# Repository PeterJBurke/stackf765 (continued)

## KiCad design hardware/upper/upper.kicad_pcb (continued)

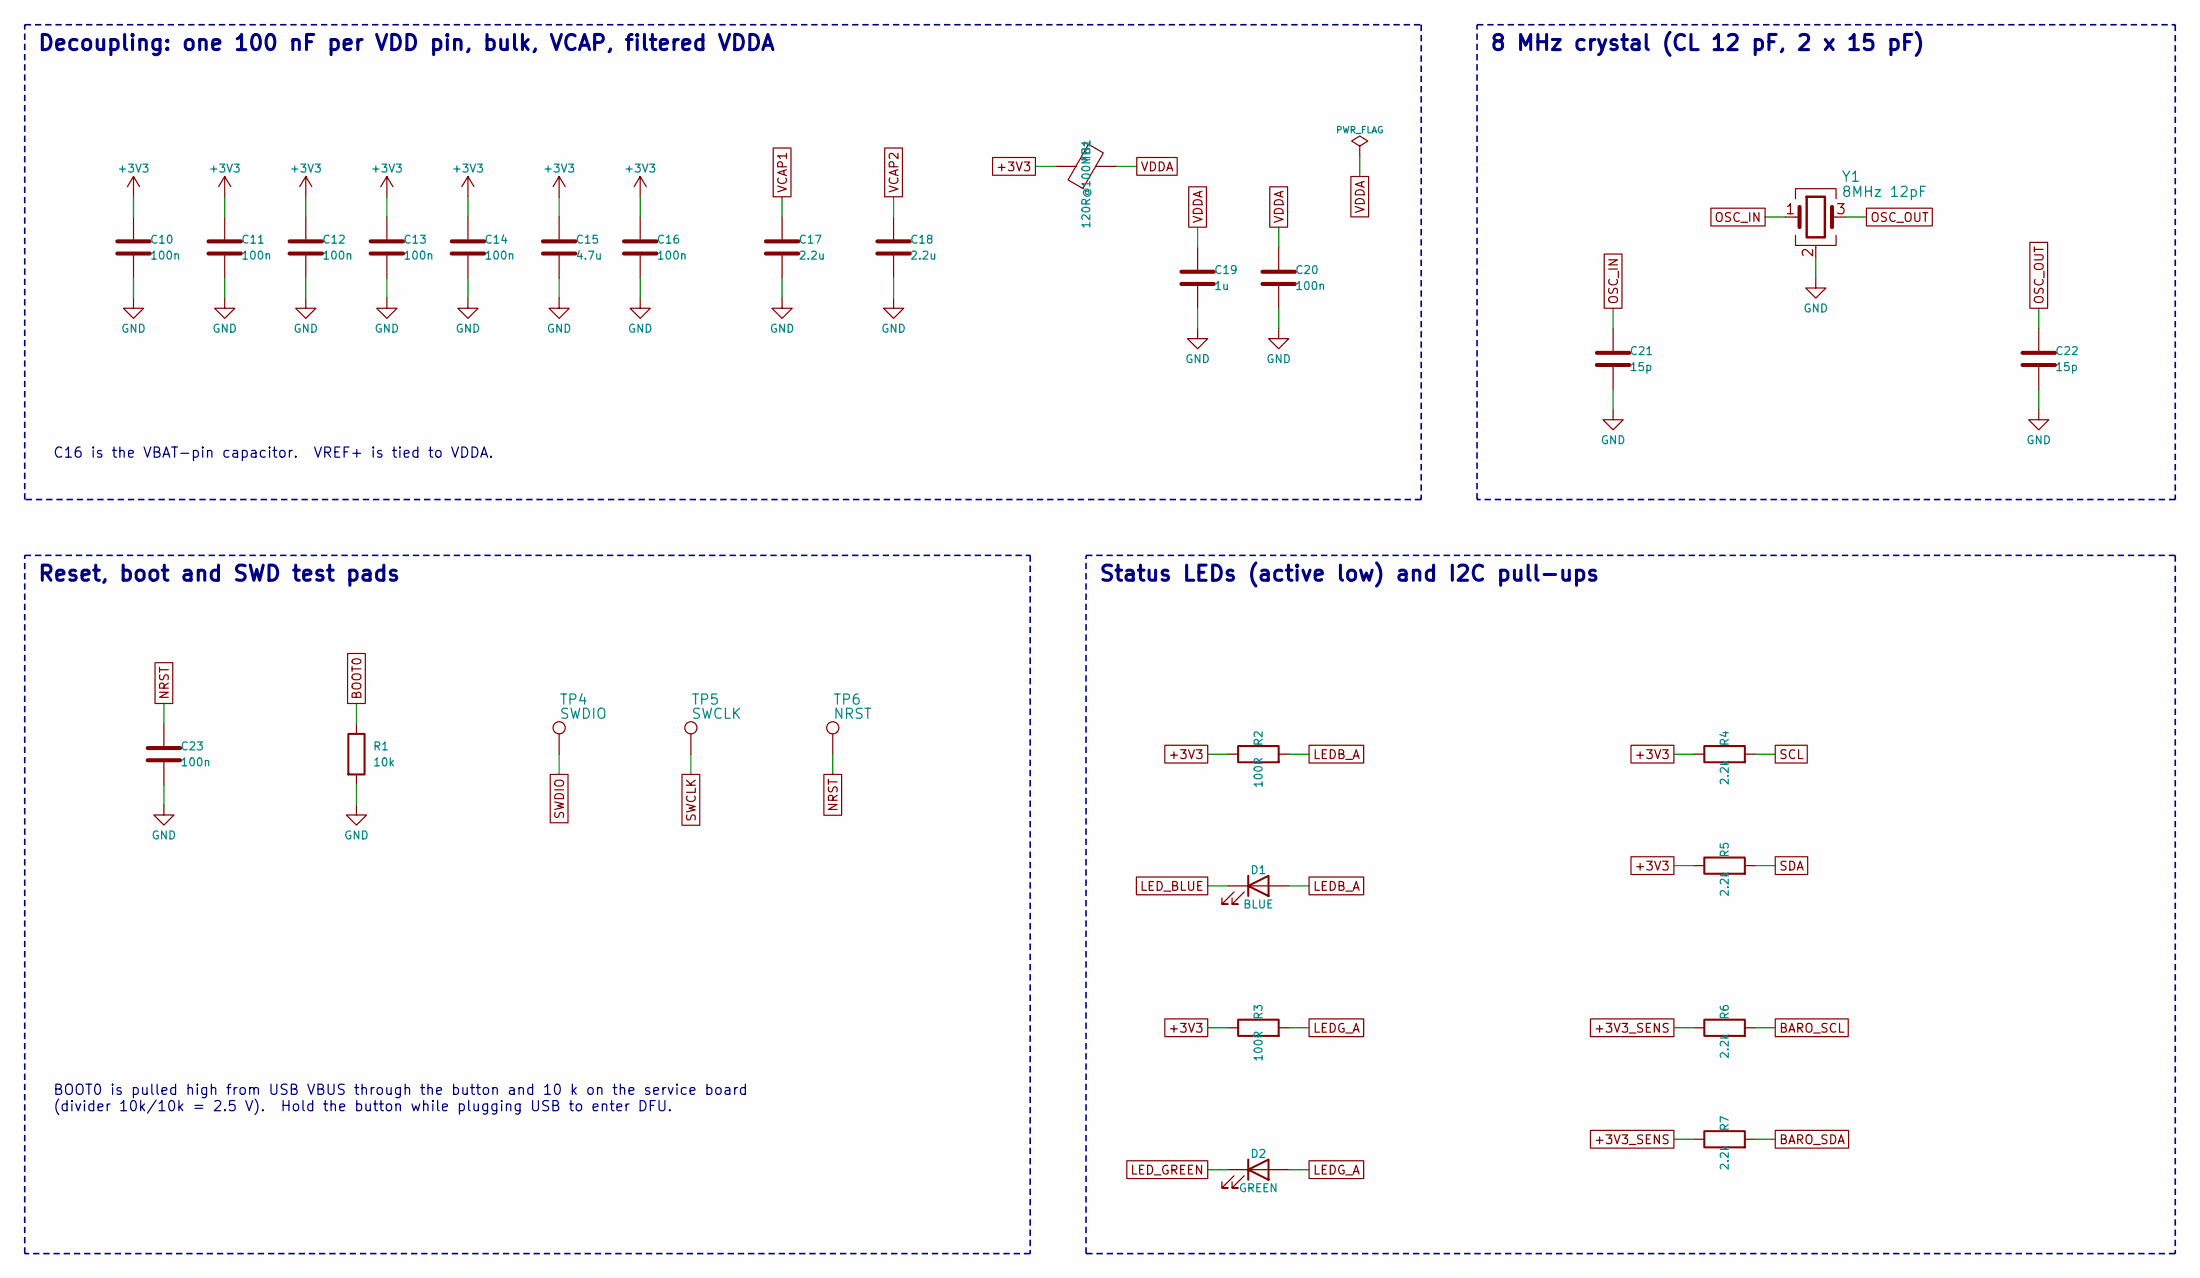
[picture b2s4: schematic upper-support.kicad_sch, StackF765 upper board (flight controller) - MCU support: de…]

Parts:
C10, C11, C12, C13, C14, C16, C20, C23: 100n; C_0402_1005Metric; MPN CL05B104KO5NNNC; LCSC C1525
C15: 4.7u; C_0603_1608Metric; MPN CL10A475KO8NNNC; LCSC C19666
C17, C18: 2.2u; C_0402_1005Metric; MPN CL05A225MQ5NSNC; LCSC C12530
C19: 1u; C_0402_1005Metric; MPN CL05A105KA5NQNC; LCSC C52923
C21, C22: 15p; C_0402_1005Metric; MPN 0402CG150J500NT; LCSC C1548
D1: BLUE; LED_0603_1608Metric; MPN NCD0603B1; LCSC C84266
D2: GREEN; LED_0603_1608Metric; MPN NCD0603G1; LCSC C84267
FB1: 120R@100MHz; L_0603_1608Metric; MPN BLM18PG121SN1D; LCSC C14709
R1: 10k; R_0402_1005Metric; MPN 0402WGF1002TCE; LCSC C25744
R2, R3: 100R; R_0402_1005Metric; MPN 0402WGF1000TCE; LCSC C25076
R4, R5, R6, R7: 2.2k; R_0402_1005Metric; MPN 0402WGF2201TCE; LCSC C25879
TP4: SWDIO; TestPoint_Pad_D1.0mm
TP5: SWCLK; TestPoint_Pad_D1.0mm
TP6: NRST; TestPoint_Pad_D1.0mm
Y1: 8MHz 12pF; Crystal_SMD_3225-4Pin_3.2x2.5mm; MPN XL2EL89COI-111YLC-8M; LCSC C2973805

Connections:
+3V3: C10.1, C11.1, C12.1, C13.1, C14.1, C15.1, C16.1, FB1.1, R2.1, R3.1, R4.1, R5.1; also elsewhere on the board
+3V3_SENS: R6.1, R7.1; also elsewhere on the board
BARO_SCL: R6.2; also elsewhere on the board
BARO_SDA: R7.2; also elsewhere on the board
BOOT0: R1.1; also elsewhere on the board
GND: C10.2, C11.2, C12.2, C13.2, C14.2, C15.2, C16.2, C17.2, C18.2, C19.2, C20.2, C21.2, C22.2, C23.2, R1.2, Y1.2 (G), Y1.4 (G); also elsewhere on the board
LEDB_A: D1.2 (A), R2.2
LEDG_A: D2.2 (A), R3.2
LED_BLUE: D1.1 (K); also elsewhere on the board
LED_GREEN: D2.1 (K); also elsewhere on the board
NRST: C23.1, TP6.1; also elsewhere on the board
OSC_IN: C21.1, Y1.1; also elsewhere on the board
OSC_OUT: C22.1, Y1.3; also elsewhere on the board
SCL: R4.2; also elsewhere on the board
SDA: R5.2; also elsewhere on the board
SWCLK: TP5.1; also elsewhere on the board
SWDIO: TP4.1; also elsewhere on the board
VCAP1: C17.1; also elsewhere on the board
VCAP2: C18.1; also elsewhere on the board
VDDA: C19.1, C20.1, FB1.2; also elsewhere on the board

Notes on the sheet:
Decoupling: one 100 nF per VDD pin, bulk, VCAP, filtered VDDA
C16 is the VBAT-pin capacitor. VREF+ is tied to VDDA.
8 MHz crystal (CL 12 pF, 2 x 15 pF)
Reset, boot and SWD test pads
BOOT0 is pulled high from USB VBUS through the button and 10 k on the service board (divider 10k/10k = 2.5 V). Hold the button while plugging USB to enter DFU.
Status LEDs (active low) and I2C pull-ups

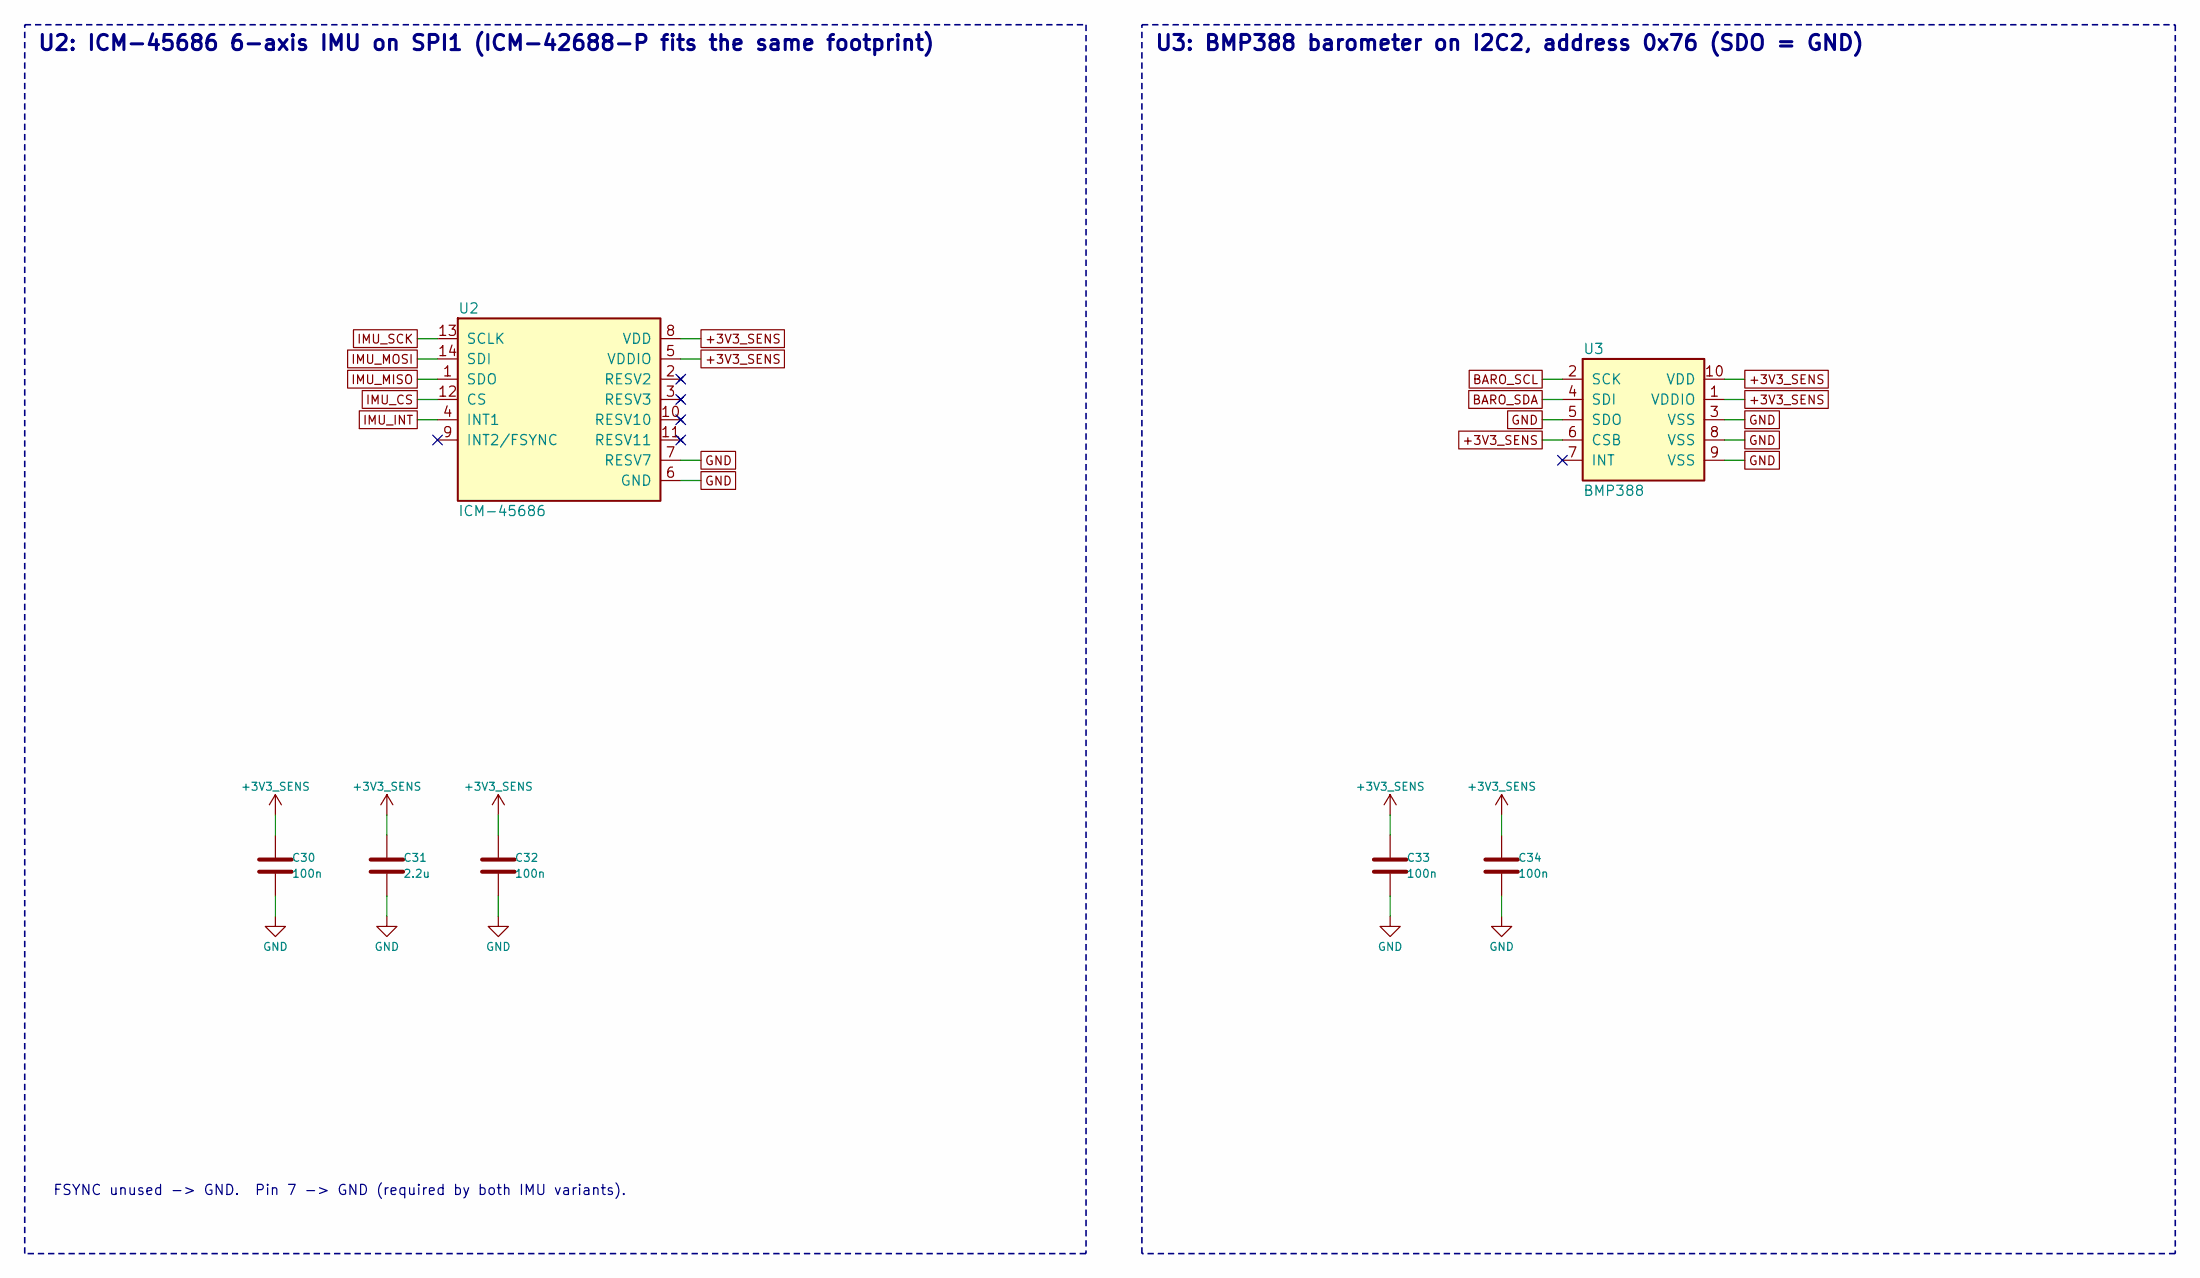
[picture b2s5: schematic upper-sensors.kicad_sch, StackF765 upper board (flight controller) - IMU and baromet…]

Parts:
C30, C32, C33, C34: 100n; C_0402_1005Metric; MPN CL05B104KO5NNNC; LCSC C1525
C31: 2.2u; C_0402_1005Metric; MPN CL05A225MQ5NSNC; LCSC C12530
U2: ICM-45686; LGA-14_3x2.5mm_P0.5mm_LayoutBorder3x4y; MPN ICM-45686; LCSC C22459454
U3: BMP388; Bosch_LGA-10_2x2mm_P0.5mm; MPN BMP388; LCSC C779278

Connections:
+3V3_SENS: C30.1, C31.1, C32.1, C33.1, C34.1, U2.5 (VDDIO), U2.8 (VDD), U3.1 (VDDIO), U3.6 (CSB), U3.10 (VDD); also elsewhere on the board
BARO_SCL: U3.2 (SCK); also elsewhere on the board
BARO_SDA: U3.4 (SDI); also elsewhere on the board
GND: C30.2, C31.2, C32.2, C33.2, C34.2, U2.6 (GND), U2.7 (RESV7), U3.3 (VSS), U3.5 (SDO), U3.8 (VSS), U3.9 (VSS); also elsewhere on the board
IMU_CS: U2.12 (CS); also elsewhere on the board
IMU_INT: U2.4 (INT1); also elsewhere on the board
IMU_MISO: U2.1 (SDO); also elsewhere on the board
IMU_MOSI: U2.14 (SDI); also elsewhere on the board
IMU_SCK: U2.13 (SCLK); also elsewhere on the board

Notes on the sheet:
U2: ICM-45686 6-axis IMU on SPI1 (ICM-42688-P fits the same footprint)
FSYNC unused -> GND. Pin 7 -> GND (required by both IMU variants).
U3: BMP388 barometer on I2C2, address 0x76 (SDO = GND)

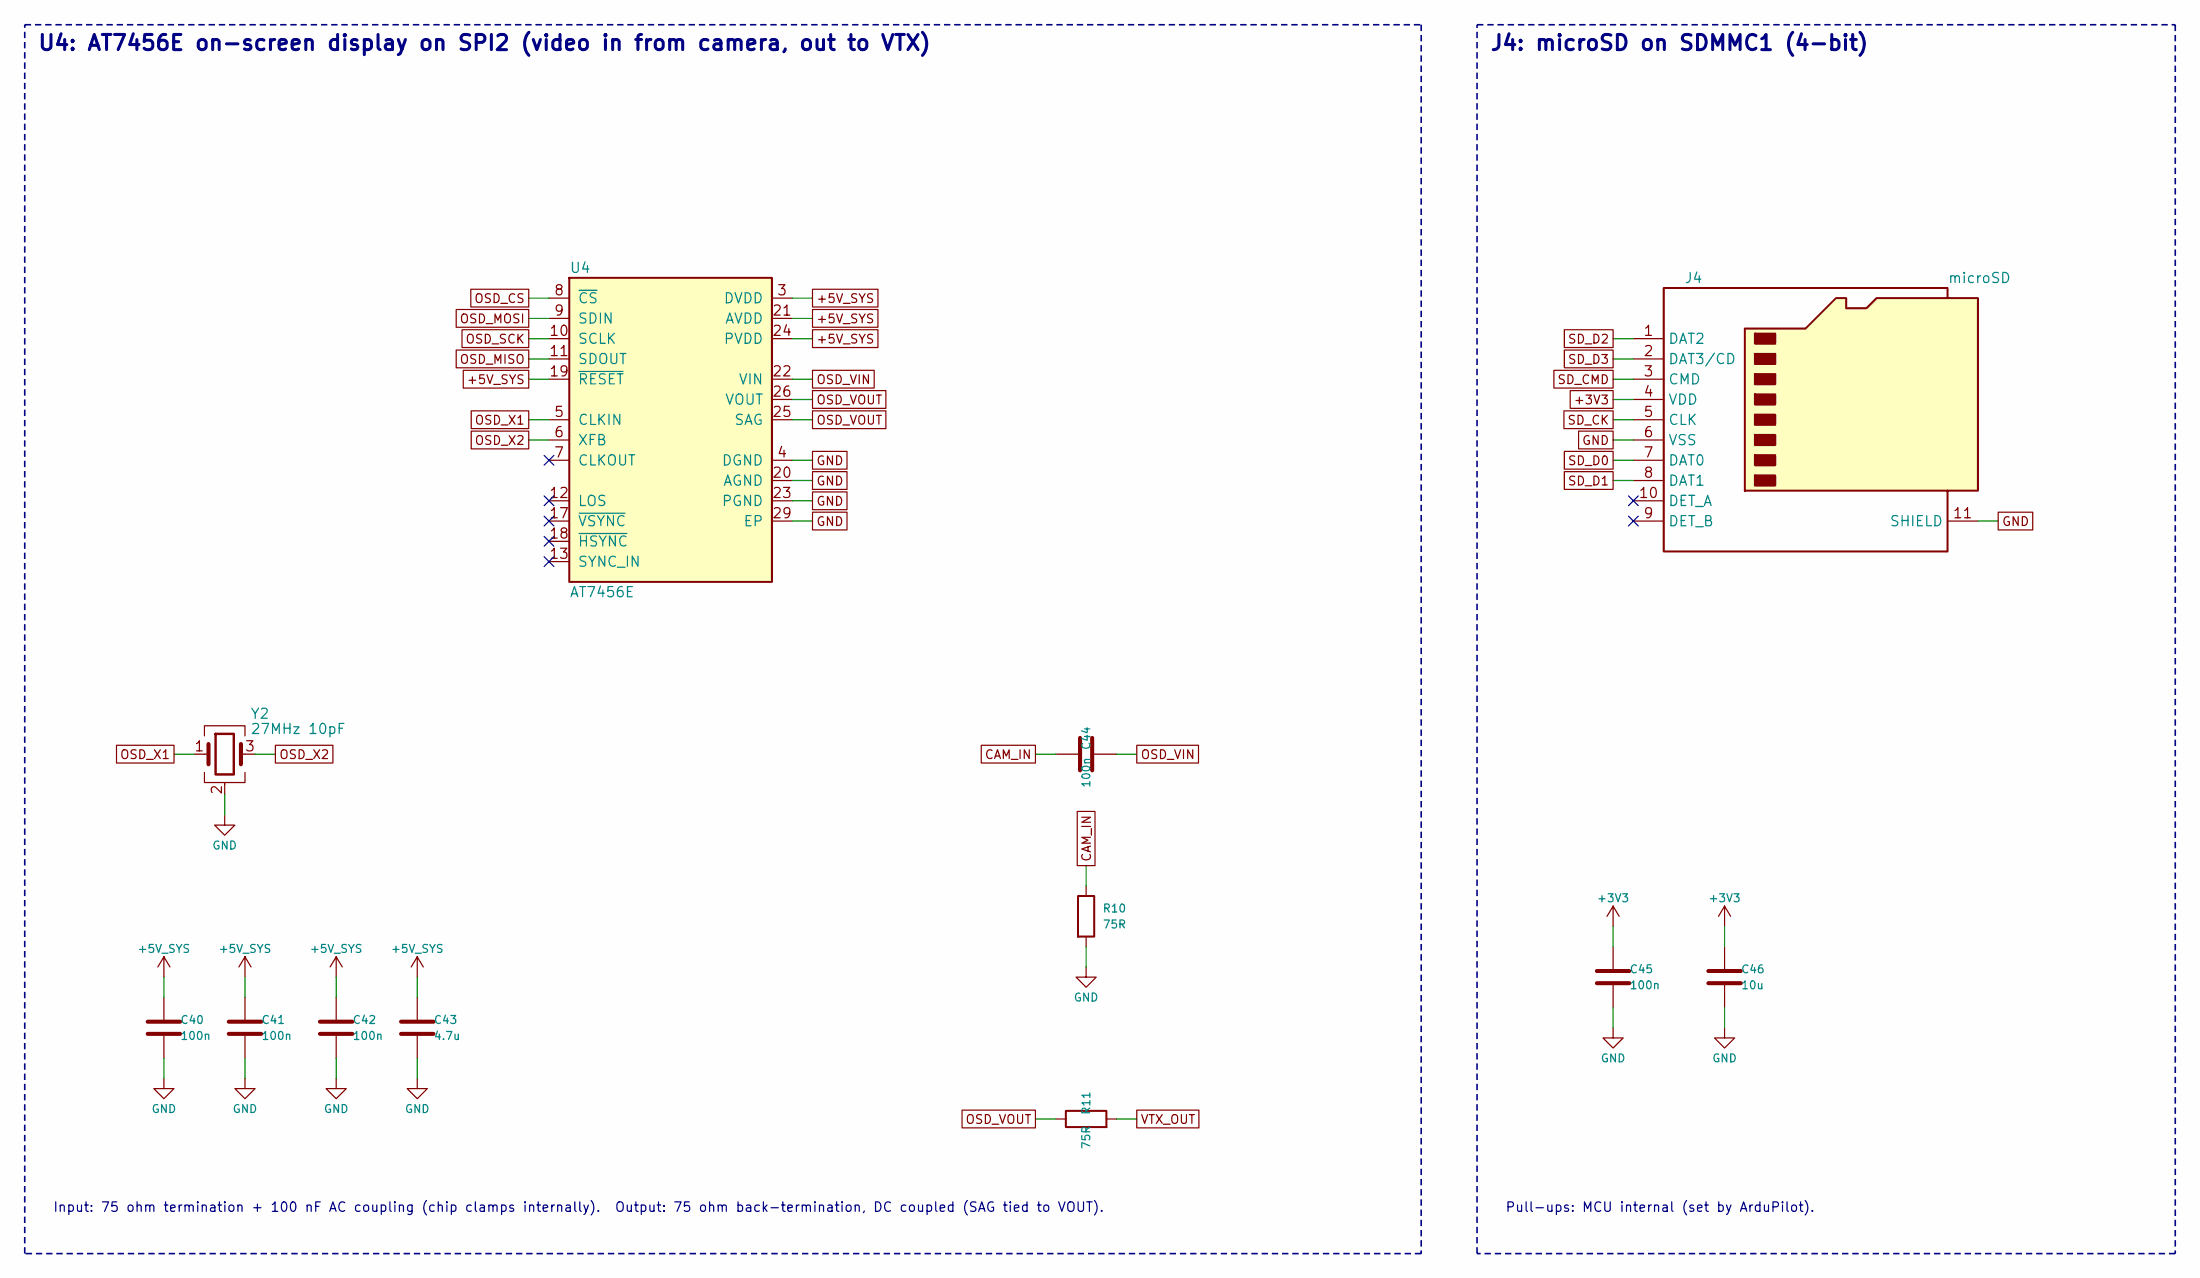
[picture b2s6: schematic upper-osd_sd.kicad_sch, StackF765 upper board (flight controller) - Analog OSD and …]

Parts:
C40, C41, C42, C44, C45: 100n; C_0402_1005Metric; MPN CL05B104KO5NNNC; LCSC C1525
C43: 4.7u; C_0603_1608Metric; MPN CL10A475KO8NNNC; LCSC C19666
C46: 10u; C_0603_1608Metric; MPN CL10A106MA8NRNC; LCSC C96446
J4: microSD; microSD_HC_Molex_104031-0811; MPN 104031-0811; LCSC C585350
R10, R11: 75R; R_0402_1005Metric; MPN 0402WGF750JTCE; LCSC C25133
U4: AT7456E; HTSSOP-28-1EP_4.4x9.7mm_P0.65mm_EP2.75x6.2mm; MPN AT7456E; LCSC C82351
Y2: 27MHz 10pF; Crystal_SMD_3225-4Pin_3.2x2.5mm; MPN X322527MMB4SI; LCSC C5210645

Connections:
+3V3: C45.1, C46.1, J4.4 (VDD); also elsewhere on the board
+5V_SYS: C40.1, C41.1, C42.1, C43.1, U4.3 (DVDD), U4.19 (~RESET), U4.21 (AVDD), U4.24 (PVDD); also elsewhere on the board
CAM_IN: C44.1, R10.1; also elsewhere on the board
GND: C40.2, C41.2, C42.2, C43.2, C45.2, C46.2, J4.6 (VSS), J4.11 (SHIELD), R10.2, U4.4 (DGND), U4.20 (AGND), U4.23 (PGND), U4.29 (EP), Y2.2 (G), Y2.4 (G); also elsewhere on the board
OSD_CS: U4.8 (~CS); also elsewhere on the board
OSD_MISO: U4.11 (SDOUT); also elsewhere on the board
OSD_MOSI: U4.9 (SDIN); also elsewhere on the board
OSD_SCK: U4.10 (SCLK); also elsewhere on the board
OSD_VIN: C44.2, U4.22 (VIN)
OSD_VOUT: R11.1, U4.25 (SAG), U4.26 (VOUT)
OSD_X1: U4.5 (CLKIN), Y2.1
OSD_X2: U4.6 (XFB), Y2.3
SD_CK: J4.5 (CLK); also elsewhere on the board
SD_CMD: J4.3 (CMD); also elsewhere on the board
SD_D0: J4.7 (DAT0); also elsewhere on the board
SD_D1: J4.8 (DAT1); also elsewhere on the board
SD_D2: J4.1 (DAT2); also elsewhere on the board
SD_D3: J4.2 (DAT3/CD); also elsewhere on the board
VTX_OUT: R11.2; also elsewhere on the board

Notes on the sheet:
U4: AT7456E on-screen display on SPI2 (video in from camera, out to VTX)
Input: 75 ohm termination + 100 nF AC coupling (chip clamps internally). Output: 75 ohm back-termination, DC coupled (SAG tied to VOUT).
J4: microSD on SDMMC1 (4-bit)
Pull-ups: MCU internal (set by ArduPilot).

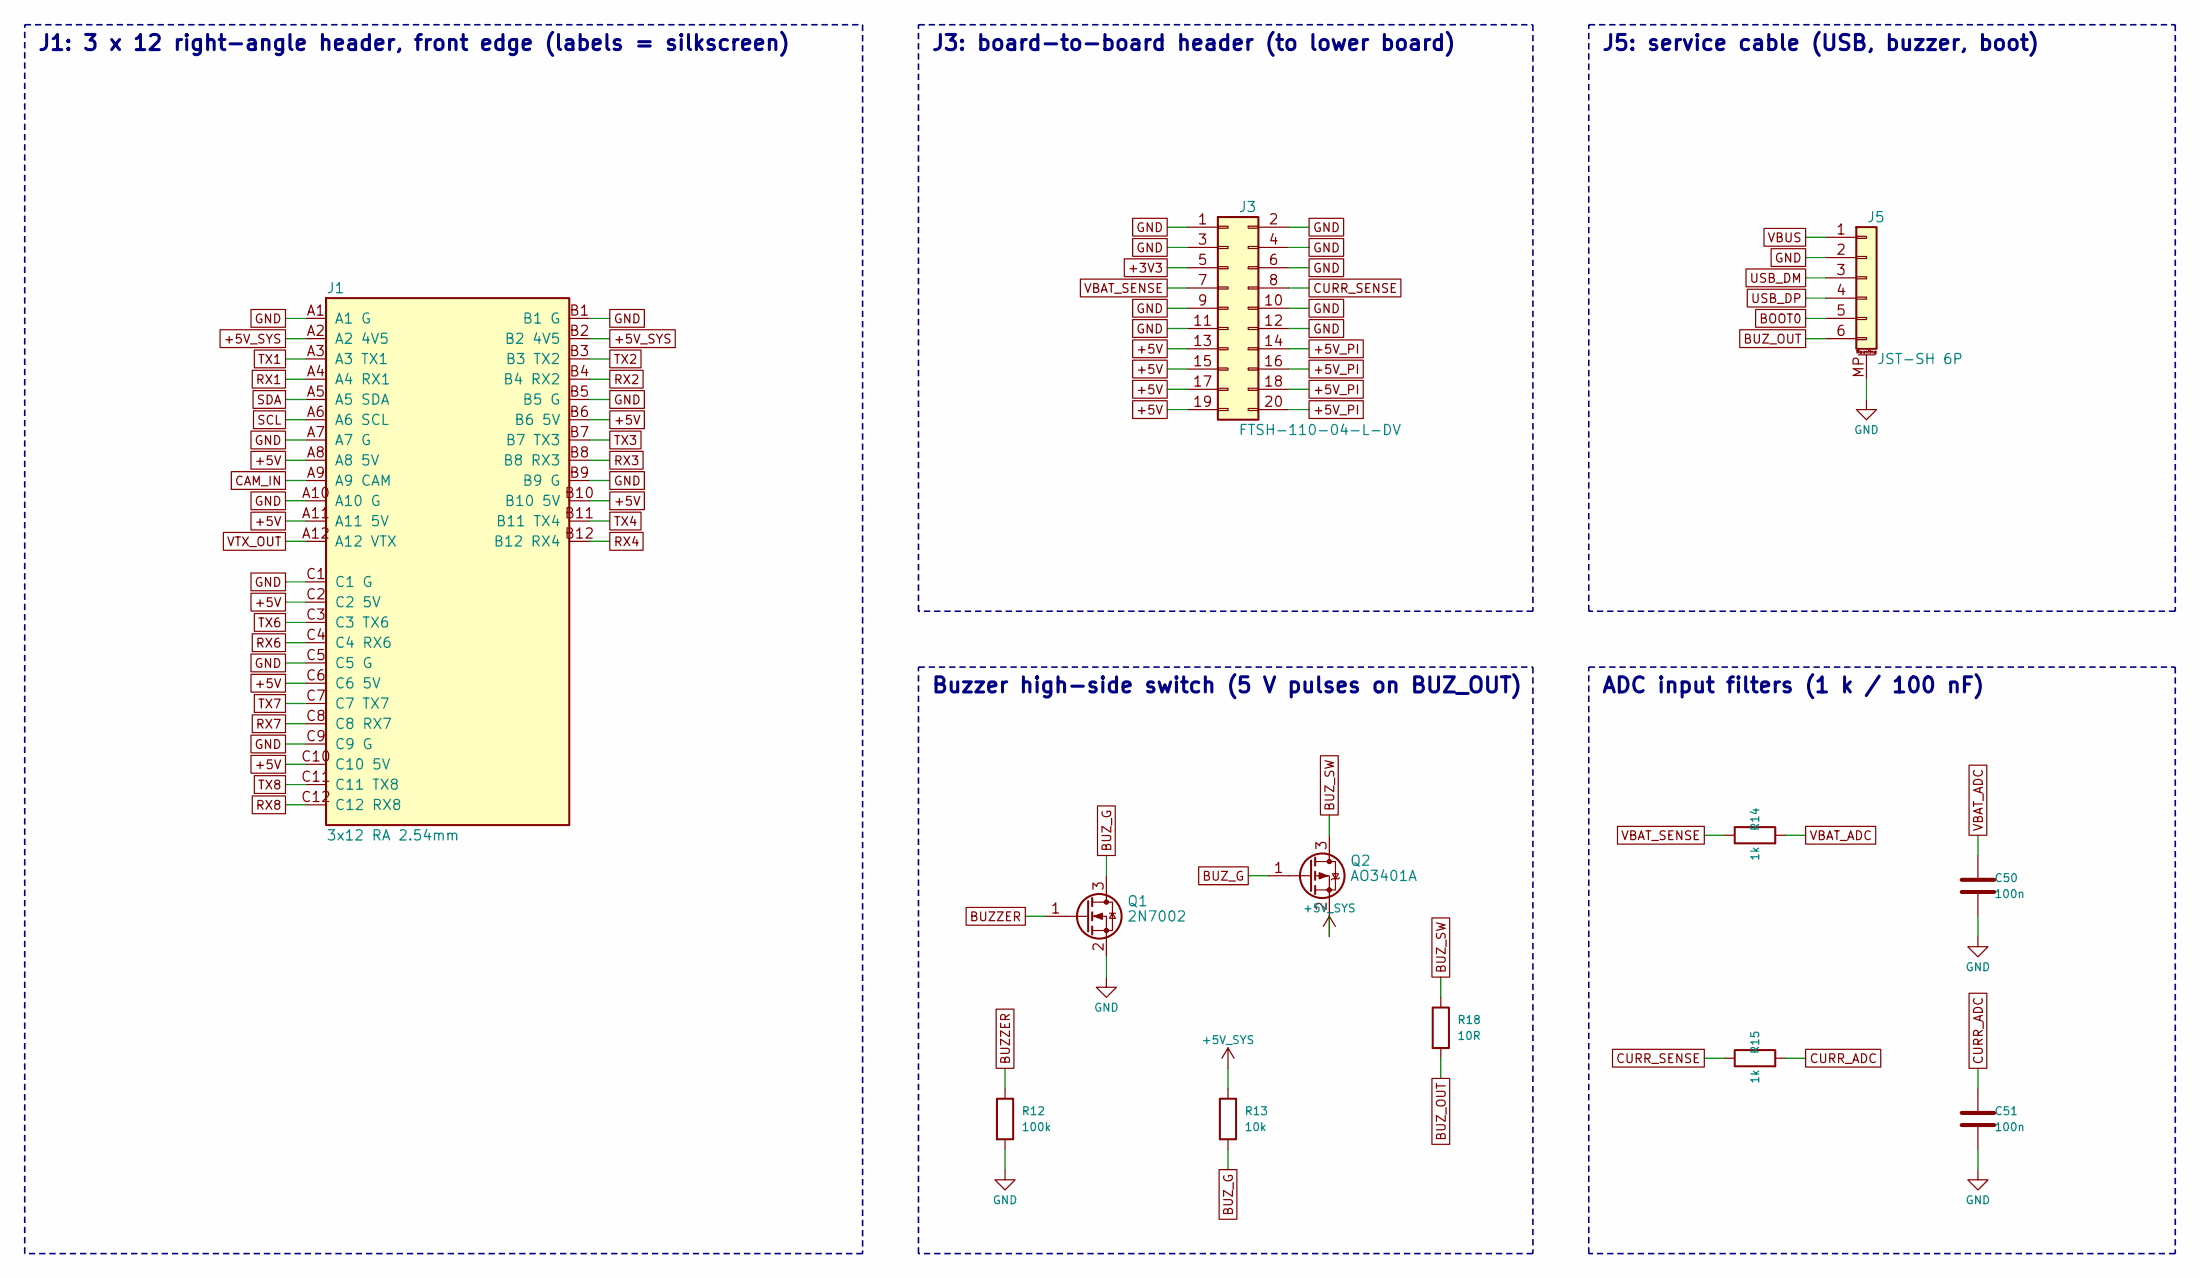
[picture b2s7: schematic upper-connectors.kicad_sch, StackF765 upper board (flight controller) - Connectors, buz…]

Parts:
C50, C51: 100n; C_0402_1005Metric; MPN CL05B104KO5NNNC; LCSC C1525
J1: 3x12 RA 2.54mm; PinHeader_3x12_P2.54mm_Horizontal; MPN PZ254-3-03-W-2.5-G0 (x4) or TSW-112-08-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; LCSC C7429379
J3: FTSH-110-04-L-DV; Samtec_FTSH-110-xx-x-DV; MPN FTSH-110-04-F-DV-TR; LCSC C7279869
J5: JST-SH 6P; JST_SH_SM06B-SRSS-TB_1x06-1MP_P1.00mm_Horizontal; MPN SM06B-SRSS-TB(LF)(SN); LCSC C160405
Q1: 2N7002; SOT-23; MPN 2N7002; LCSC C8545
Q2: AO3401A; SOT-23; MPN AO3401A; LCSC C15127
R12: 100k; R_0402_1005Metric; MPN 0402WGF1003TCE; LCSC C25741
R13: 10k; R_0402_1005Metric; MPN 0402WGF1002TCE; LCSC C25744
R14, R15: 1k; R_0402_1005Metric; MPN 0402WGF1001TCE; LCSC C11702
R18: 10R; R_1206_3216Metric; MPN MFCR1206F10R0QHR; LCSC C42460620

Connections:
+3V3: J3.5; also elsewhere on the board
+5V: J1.A8 (A8 5V), J1.A11 (A11 5V), J1.B6 (B6 5V), J1.B10 (B10 5V), J1.C2 (C2 5V), J1.C6 (C6 5V), J1.C10 (C10 5V), J3.13, J3.15, J3.17, J3.19; also elsewhere on the board
+5V_PI: J3.14, J3.16, J3.18, J3.20; also elsewhere on the board
+5V_SYS: J1.A2 (A2 4V5), J1.B2 (B2 4V5), Q2.2 (S), R13.1; also elsewhere on the board
BOOT0: J5.5; also elsewhere on the board
BUZZER: Q1.1 (G), R12.1; also elsewhere on the board
BUZ_G: Q1.3 (D), Q2.1 (G), R13.2
BUZ_OUT: J5.6, R18.2
BUZ_SW: Q2.3 (D), R18.1
CAM_IN: J1.A9 (A9 CAM); also elsewhere on the board
CURR_ADC: C51.1, R15.2; also elsewhere on the board
CURR_SENSE: J3.8, R15.1
GND: C50.2, C51.2, J1.A1 (A1 G), J1.A7 (A7 G), J1.A10 (A10 G), J1.B1 (B1 G), J1.B5 (B5 G), J1.B9 (B9 G), J1.C1 (C1 G), J1.C5 (C5 G), J1.C9 (C9 G), J3.1, J3.2, J3.3, J3.4, J3.6, J3.9, J3.10, J3.11, J3.12, J5.2, J5.MP (MountPin), Q1.2 (S), R12.2; also elsewhere on the board
RX1: J1.A4 (A4 RX1); also elsewhere on the board
RX2: J1.B4 (B4 RX2); also elsewhere on the board
RX3: J1.B8 (B8 RX3); also elsewhere on the board
RX4: J1.B12 (B12 RX4); also elsewhere on the board
RX6: J1.C4 (C4 RX6); also elsewhere on the board
RX7: J1.C8 (C8 RX7); also elsewhere on the board
RX8: J1.C12 (C12 RX8); also elsewhere on the board
SCL: J1.A6 (A6 SCL); also elsewhere on the board
SDA: J1.A5 (A5 SDA); also elsewhere on the board
TX1: J1.A3 (A3 TX1); also elsewhere on the board
TX2: J1.B3 (B3 TX2); also elsewhere on the board
TX3: J1.B7 (B7 TX3); also elsewhere on the board
TX4: J1.B11 (B11 TX4); also elsewhere on the board
TX6: J1.C3 (C3 TX6); also elsewhere on the board
TX7: J1.C7 (C7 TX7); also elsewhere on the board
TX8: J1.C11 (C11 TX8); also elsewhere on the board
USB_DM: J5.3; also elsewhere on the board
USB_DP: J5.4; also elsewhere on the board
VBAT_ADC: C50.1, R14.2; also elsewhere on the board
VBAT_SENSE: J3.7, R14.1
VBUS: J5.1; also elsewhere on the board
VTX_OUT: J1.A12 (A12 VTX); also elsewhere on the board

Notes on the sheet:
J1: 3 x 12 right-angle header, front edge (labels = silkscreen)
J3: board-to-board header (to lower board)
J5: service cable (USB, buzzer, boot)
Buzzer high-side switch (5 V pulses on BUZ_OUT)
ADC input filters (1 k / 100 nF)

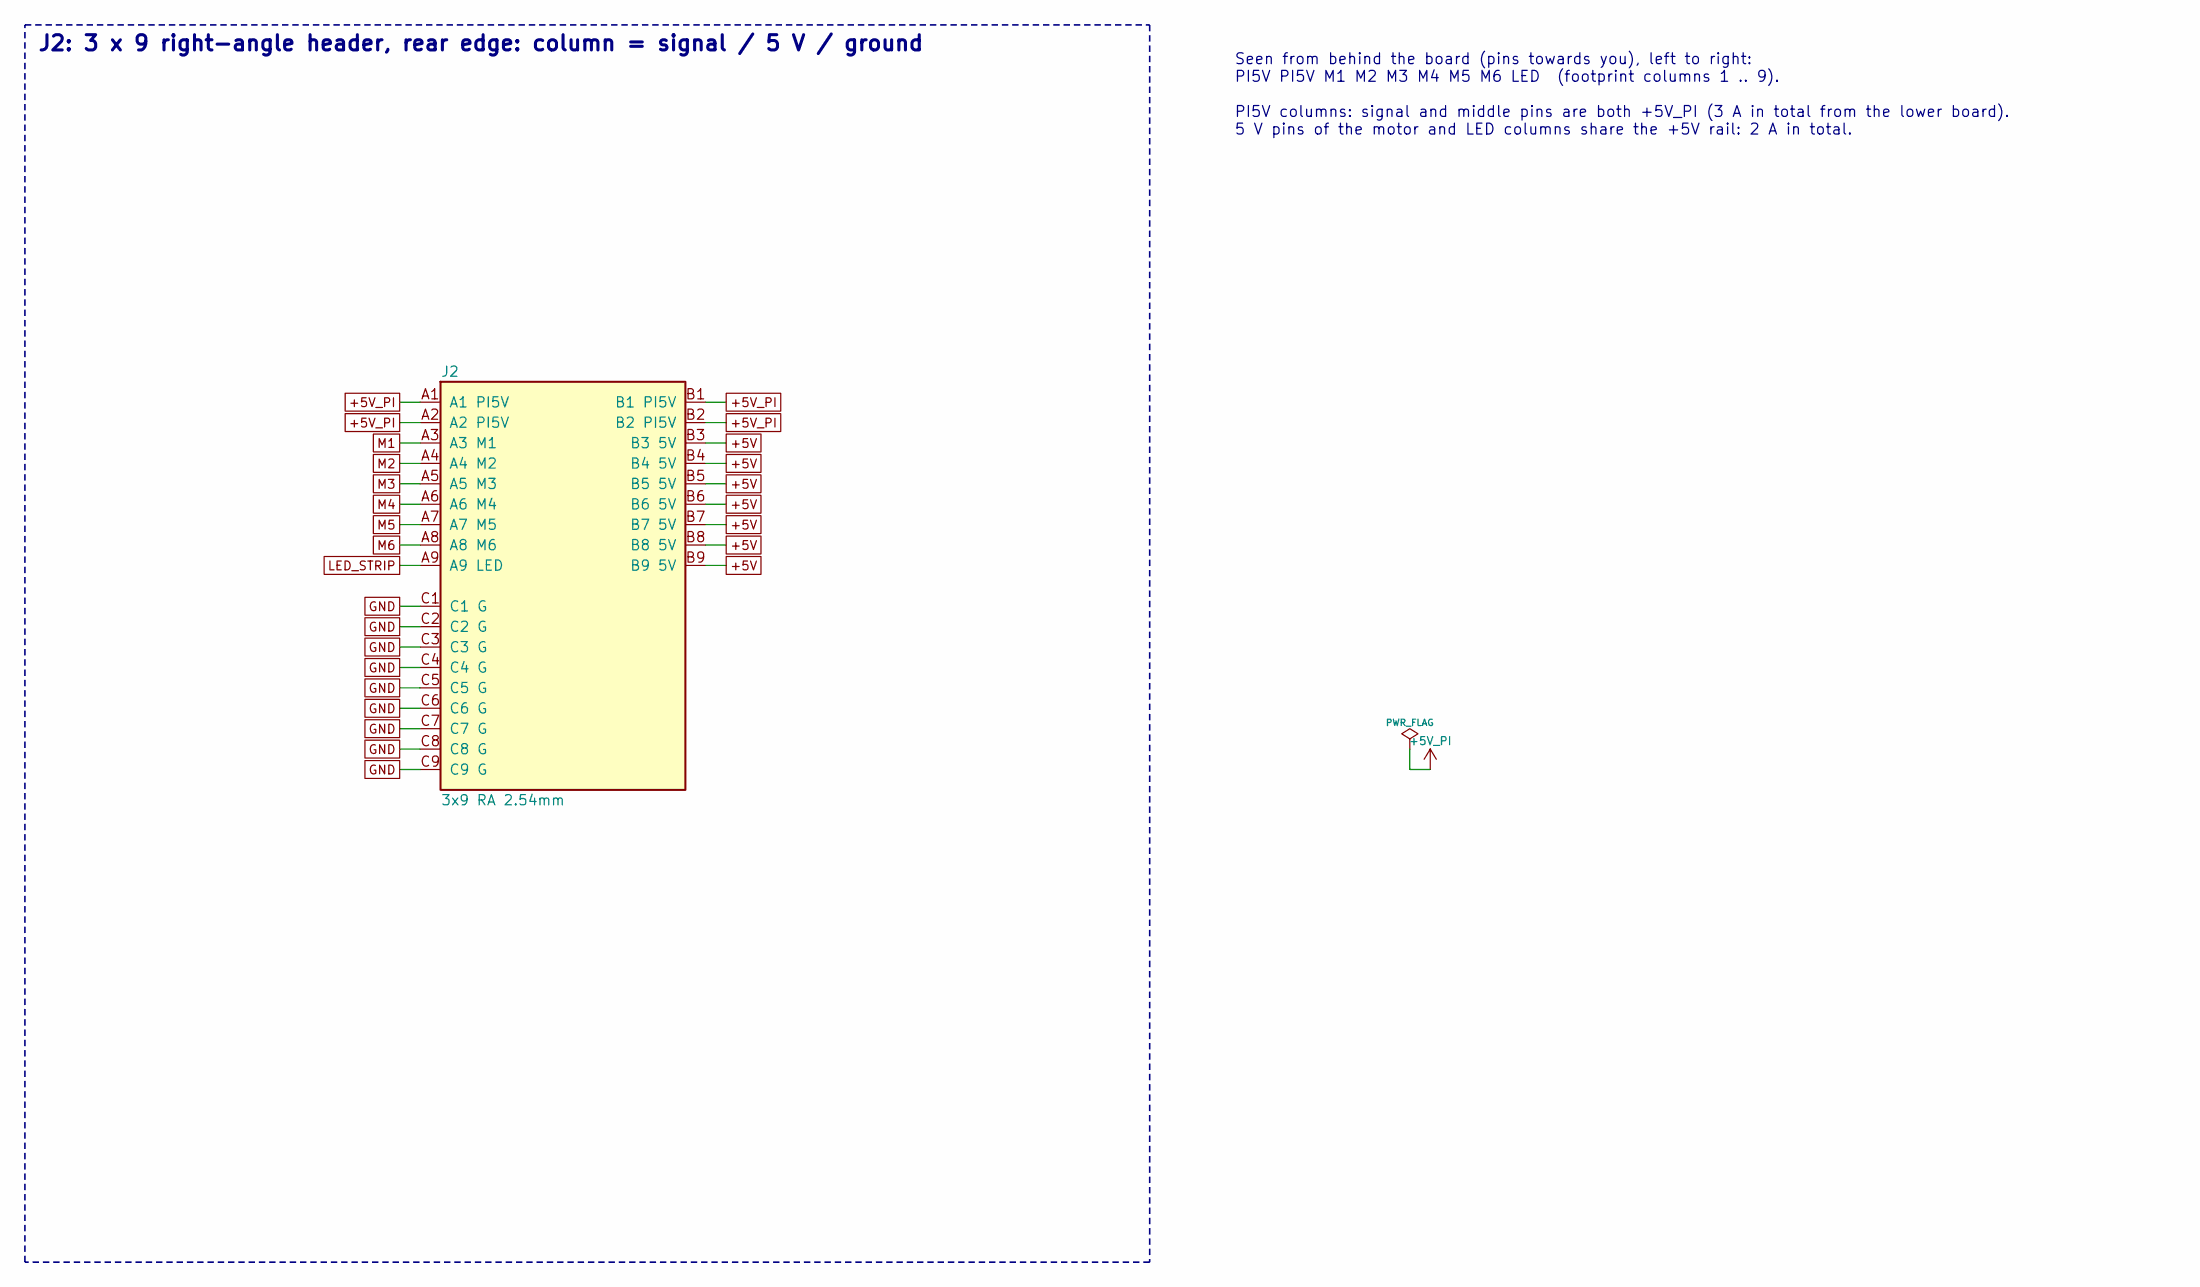
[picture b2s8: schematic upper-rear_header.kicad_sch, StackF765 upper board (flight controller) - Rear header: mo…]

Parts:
J2: 3x9 RA 2.54mm; PinHeader_3x09_P2.54mm_Horizontal; MPN PZ254-3-03-W-2.5-G0 (x3); LCSC C7429379

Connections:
+5V: J2.B3 (B3 5V), J2.B4 (B4 5V), J2.B5 (B5 5V), J2.B6 (B6 5V), J2.B7 (B7 5V), J2.B8 (B8 5V), J2.B9 (B9 5V); also elsewhere on the board
+5V_PI: J2.A1 (A1 PI5V), J2.A2 (A2 PI5V), J2.B1 (B1 PI5V), J2.B2 (B2 PI5V); also elsewhere on the board
GND: J2.C1 (C1 G), J2.C2 (C2 G), J2.C3 (C3 G), J2.C4 (C4 G), J2.C5 (C5 G), J2.C6 (C6 G), J2.C7 (C7 G), J2.C8 (C8 G), J2.C9 (C9 G); also elsewhere on the board
LED_STRIP: J2.A9 (A9 LED); also elsewhere on the board
M1: J2.A3 (A3 M1); also elsewhere on the board
M2: J2.A4 (A4 M2); also elsewhere on the board
M3: J2.A5 (A5 M3); also elsewhere on the board
M4: J2.A6 (A6 M4); also elsewhere on the board
M5: J2.A7 (A7 M5); also elsewhere on the board
M6: J2.A8 (A8 M6); also elsewhere on the board

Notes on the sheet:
J2: 3 x 9 right-angle header, rear edge: column = signal / 5 V / ground
Seen from behind the board (pins towards you), left to right: PI5V PI5V M1 M2 M3 M4 M5 M6 LED (footprint columns 1 .. 9). PI5V columns: signal and middle pins are both +5V_PI (3 A in total from the lower board). 5 V pins of the motor and LED columns share the +5V rail: 2 A in total.

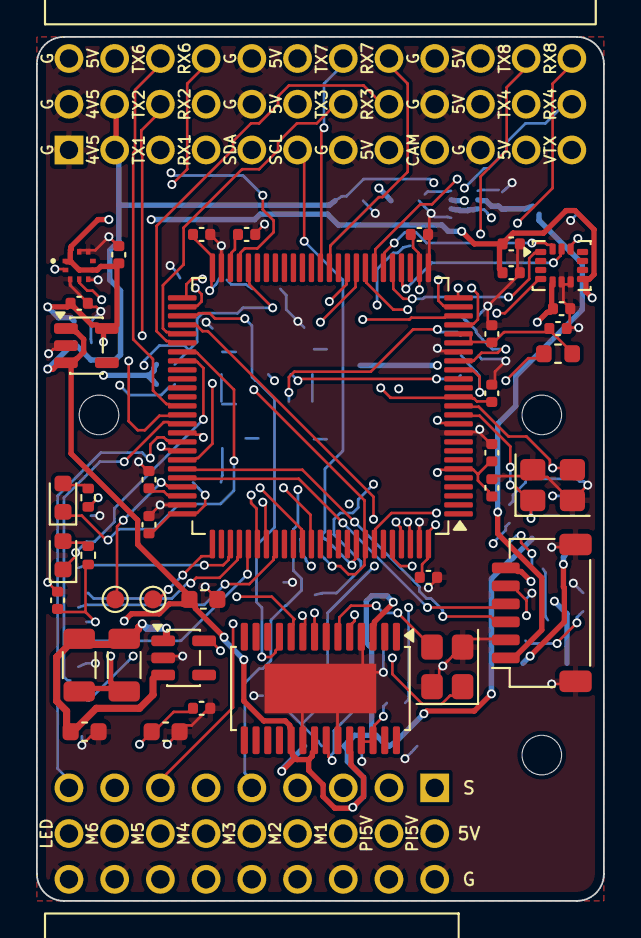
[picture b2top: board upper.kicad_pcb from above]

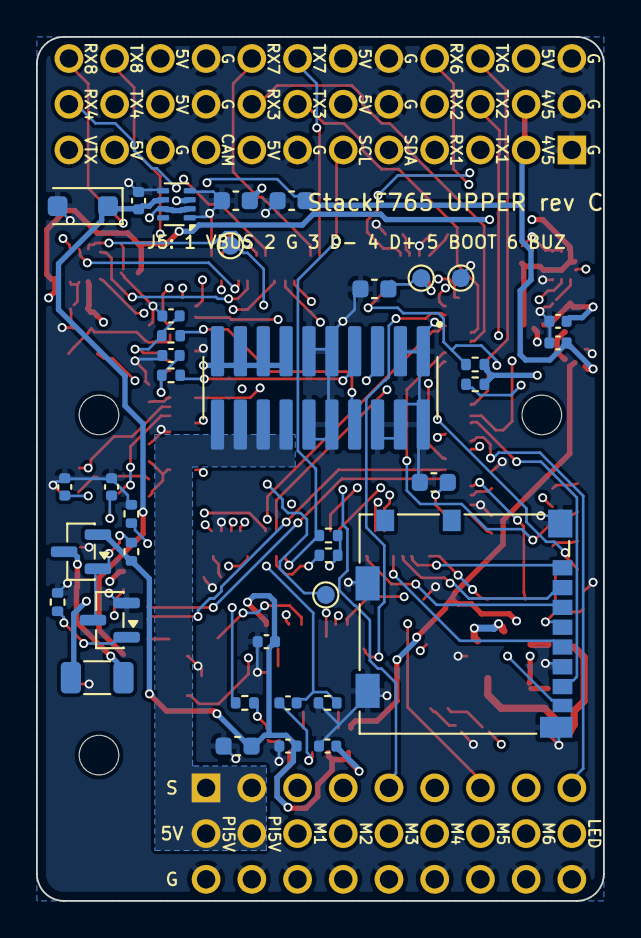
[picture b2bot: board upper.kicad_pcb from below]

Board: 6 copper layers, 31.5 x 48.0 mm, 82 parts (38 on the bottom side), 77 nets.

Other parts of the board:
H: (no value)
H#2, H#3: (no value)

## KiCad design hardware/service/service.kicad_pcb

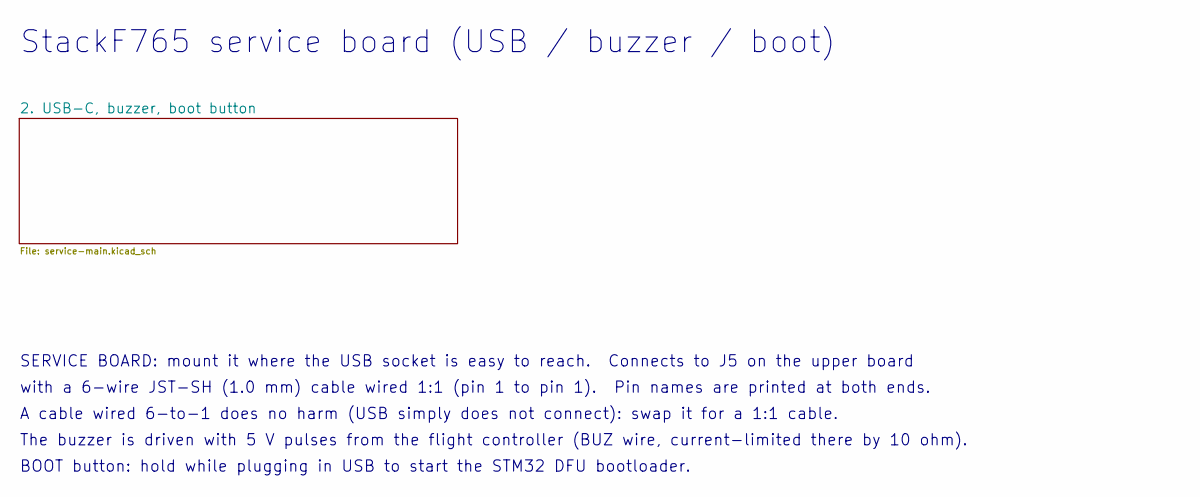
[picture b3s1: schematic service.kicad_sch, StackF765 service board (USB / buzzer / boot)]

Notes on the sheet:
StackF765 service board (USB / buzzer / boot)
SERVICE BOARD: mount it where the USB socket is easy to reach. Connects to J5 on the upper board
with a 6-wire JST-SH (1.0 mm) cable wired 1:1 (pin 1 to pin 1). Pin names are printed at both ends.
A cable wired 6-to-1 does no harm (USB simply does not connect): swap it for a 1:1 cable.
The buzzer is driven with 5 V pulses from the flight controller (BUZ wire, current-limited there by 10 ohm).
BOOT button: hold while plugging in USB to start the STM32 DFU bootloader.
